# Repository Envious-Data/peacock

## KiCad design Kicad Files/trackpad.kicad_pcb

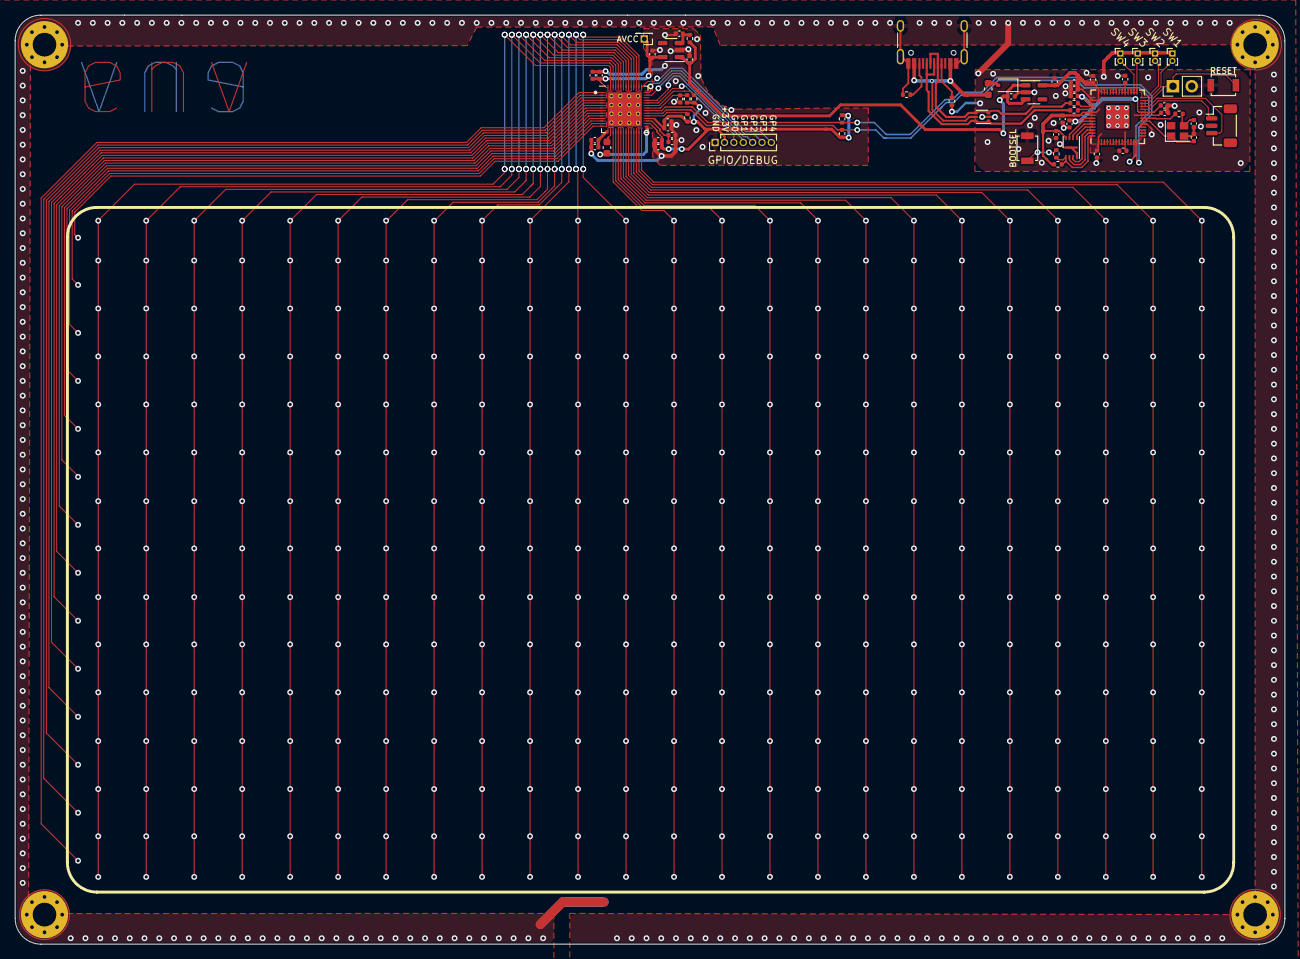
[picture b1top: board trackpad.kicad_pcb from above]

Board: 2 copper layers, 172.0 x 125.8 mm, 68 parts (0 on the bottom side), 46 nets.

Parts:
C1, C4, C14, C15, C18, C22, C28, C30: 1µ; C_0402_1005Metric
C2, C3, C5, C6, C7, C8, C9, C10, C11, C37: 100n; C_0402_1005Metric
C12, C13: 15p; C_0402_1005Metric
C16, C39: 10nF; C_0402_1005Metric
C17: 2.2nF; C_0603_1608Metric
C19, C21, C23, C25, C27: 22n; C_0402_1005Metric
C20, C24, C26: 2.2µ; C_0402_1005Metric
D1: B5817; D_SOD-323
F1: Polyfuse; Fuse_0603_1608Metric
H1, H2, H3, H4: MountingHole_Pad; MountingHole_3.2mm_M3_Pad_Via
J1: type-c-31-m-12; USB_C_Receptacle_HRO_TYPE-C-31-M-12
J3: JST 3P; JST_SH_BM03B-SRSS-TB_1x03-1MP_P1.00mm_Vertical
J5: Conn_01x07_Pin; PinHeader_1x07_P1.27mm_Vertical
J9: Conn_01x02_Pin; PinHeader_1x02_P2.54mm_Vertical
J10: Conn_01x01_Pin; PinHeader_1x01_P1.27mm_Vertical
R1, R11, R12, R17: 10k; R_0402_1005Metric
R2, R3: 1k; R_0402_1005Metric
R6, R7: 5.1k; R_0402_1005Metric
R8, R9: 27; R_0402_1005Metric
R10: 12k; R_0402_1005Metric
R13, R14: 3.3k; R_0402_1005Metric
SW1, SW2, SW3, SW4: SW_Push; PinHeader_1x02_P1.00mm_Vertical
SW_BOOT1: SW_Push; SW_SPST_B3U-1000P
SW_RST1: SW_Push; SW_SPST_B3U-1000P
U1: RP2040; QFN-56-1EP_7x7mm_P0.4mm_EP3.2x3.2mm
U2: W25Q16JVUXIQ; USON-8-1EP_3x2mm_P0.5mm_EP0.25x1.65mm
U3, U5: MIC5504-3.3YM5; SOT-23-5
U4: mXT336UD-MAU002; QFN-56_EP_6x6_Pitch0.35mm
U7: USBLC6-2P6; SOT-666
Y1: Crystal_GND24; Crystal_SMD_2520-4Pin_2.5x2.0mm

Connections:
3V3: C4.1, C5.1, C6.1, C7.1, C8.1, C9.1, C10.1, C11.1, C30.1, C37.2, R1.1, U1.1 (IOVDD), U1.10 (IOVDD), U1.22 (IOVDD), U1.33 (IOVDD), U1.42 (IOVDD), U1.43 (ADC_AVDD), U1.44 (VREG_IN), U1.48 (USB_VDD), U1.49 (IOVDD), U2.8 (VCC), U3.5 (VOUT)
5V: C14.1, C15.1, D1.1 (K), R17.1, U3.1 (VIN), U3.3 (EN), U5.1 (VIN)
+1V1: C1.1, C2.1, C3.1, U1.23 (DVDD), U1.45 (VREG_VOUT), U1.50 (DVDD)
+3.3VA: C20.2, C21.2, C28.1, J10.1, U4.56 (AVDD), U5.5 (VOUT)
+3V3: C24.2, C25.2, C26.2, C27.2, J5.2, R10.1, R11.1, R12.1, R13.1, R14.1, U4.30 (VDD), U4.32 (VDDIO)
/Macropad/D+: J1.A6 (D+), J1.B6 (D+), R8.2, U7.1 (I/O1), U7.6 (I/O1)
/Macropad/D-: J1.A7 (D-), J1.B7 (D-), R9.2, U7.3 (I/O2), U7.4 (I/O2)
/Macropad/RUN: J9.1, SW_RST1.1, U1.26 (RUN)
/Macropad/SW1: SW1.2, U1.27 (GPIO16)
/Macropad/SW2: SW2.2, U1.28 (GPIO17)
/Macropad/SW3: SW3.2, U1.29 (GPIO18)
/Macropad/SW4: SW4.2, U1.30 (GPIO19)
/Sensor/CHANGE: R11.2, U4.37 (CHG)
/Sensor/GPIO0: J5.3, U4.38 (GPIO0)
/Sensor/GPIO1: J5.4, U4.39 (GPIO1)
/Sensor/GPIO2: J5.5, U4.41 (GPIO2)
/Sensor/GPIO3: J5.6, U4.42 (GPIO3)
/Sensor/GPIO4: J5.7, U4.43 (GPIO4)
/Sensor/RESET: C16.1, R10.2, U4.36 (RESET)
GND: C1.2, C2.2, C3.2, C4.2, C5.2, C6.2, C7.2, C8.2, C9.2, C10.2, C11.2, C12.2, C13.2, C14.2, C15.2, C16.2, C18.2, C19.2, C20.1, C21.1, C22.1, C23.1, C24.1, C25.1, C26.1, C27.1, C28.2, C30.2, C37.1, C39.2, H1.1, H2.1, H3.1, H4.1, J1.A1 (GND), J1.A12 (GND), J1.B1 (GND), J1.B12 (GND), J1.S1 (SHIELD), J3.2, J5.1, J9.2, R6.2, R7.2, SW1.1, SW2.1, SW3.1, SW4.1, SW_BOOT1.1, SW_RST1.2, U1.19 (TESTEN), U1.57 (GND), U2.4 (GND), U2.9 (EP), U3.2 (GND), U4.57 (GND), U5.2 (GND), U7.2 (GND), Y1.2, Y1.4
unnamed: C13.1, R3.2, Y1.3
unnamed: D1.2 (A), F1.1
unnamed: J1.A5 (CC1), R6.1
unnamed: J1.B5 (CC2), R7.1
unnamed: J3.1, U1.24 (SWCLK)
unnamed: J3.3, U1.25 (SWD)
unnamed: R2.1, SW_BOOT1.2
unnamed: U1.52 (QSPI_SCLK), U2.6 (CLK)
unnamed: U1.53 (QSPI_SD0), U2.5 (DI(IO0))
unnamed: U1.55 (QSPI_SD1), U2.2 (DO(IO1))
unnamed: U1.54 (QSPI_SD2), U2.3 (IO2)
unnamed: U1.51 (QSPI_SD3), U2.7 (IO3)
unnamed: R1.2, R2.2, U1.56 (QSPI_SS), U2.1 (~CS)
unnamed: R9.1, U1.46 (USB_DM)
unnamed: R8.1, U1.47 (USB_DP)
unnamed: C12.1, U1.20 (XIN), Y1.1
unnamed: R3.1, U1.21 (XOUT)
unnamed: C17.2, U4.29 (EXCAP0)
unnamed: C17.1, U4.16 (EXCAP1)
unnamed: R12.2, U4.33 (TEST)
unnamed: C22.2, C23.2, U4.31 (VDDCORE)
unnamed: C18.1, C19.1, U4.15 (XVDD)
unnamed: C39.1, R17.2, U5.3 (EN)
SCL: R13.2, U1.14 (GPIO11), U4.35 (SCL)
SDA: R14.2, U1.13 (GPIO10), U4.34 (SDA)
VBUS: F1.2, J1.A4 (VBUS), J1.A9 (VBUS), J1.B4 (VBUS), J1.B9 (VBUS), U7.5 (VBUS)

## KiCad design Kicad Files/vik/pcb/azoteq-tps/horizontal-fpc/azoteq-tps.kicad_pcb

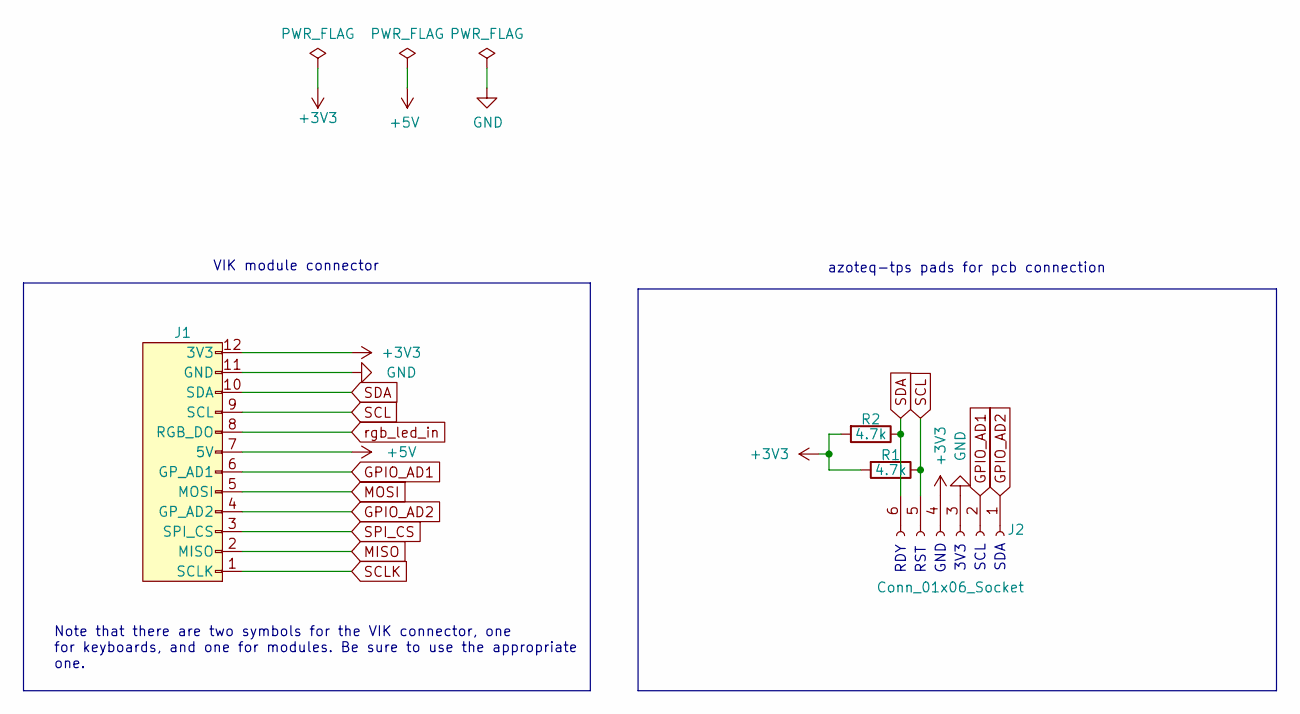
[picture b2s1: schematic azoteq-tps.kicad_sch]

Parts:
J1: vik-module-connector-horizontal-mini; LCSC C2919479
J2: Conn_01x06_Socket; Pad_06_2.00mm
R1, R2: 4.7k; R_0805_2012Metric_Pad1.20x1.40mm_HandSolder; LCSC C115310

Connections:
+3V3: J1.12 (3V3), J2.4, R1.2, R2.2
+5V: J1.7 (5V)
GND: J1.11 (GND), J2.3
GPIO_AD1: J1.6 (GPIO_AD1), J2.2
GPIO_AD2: J1.4 (GPIO_AD2), J2.1
MISO: J1.2 (MISO)
MOSI: J1.5 (MOSI)
SCL: J1.9 (SCL), J2.5, R1.1
SCLK: J1.1 (SCLK)
SDA: J1.10 (SDA), J2.6, R2.1
SPI_CS: J1.3 (SPI_CS)
rgb_led_in: J1.8 (RGB_LED_IN)

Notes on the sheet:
GND
RST
SCL
Note that there are two symbols for the VIK connector, one for keyboards, and one for modules. Be sure to use the appropriate one.
azoteq-tps pads for pcb connection
3V3
SDA
VIK module connector
RDY

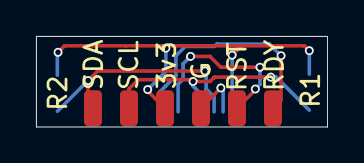
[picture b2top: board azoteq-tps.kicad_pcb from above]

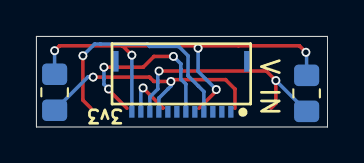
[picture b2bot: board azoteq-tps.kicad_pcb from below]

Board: 2 copper layers, 16.2 x 5.0 mm, 4 parts (3 on the bottom side), 6 nets.

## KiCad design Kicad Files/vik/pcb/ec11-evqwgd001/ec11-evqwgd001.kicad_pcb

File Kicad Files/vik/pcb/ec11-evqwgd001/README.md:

# ec11 evqwgd001 vik module

## Overview

This is a simple EC11 and EVQWGD001 vik module. It has support for 4 upwards facing SK6812 mini-e leds, in case you want to add a little pizzazz to your encoder.

Please note that this PCB does **not** support the click, only rotation of the encoder.

## Fabrication and BOM

For PCB fabrication, you can use the files in the production folder.

* gerbers.zip - the file used to fabricate the pcb
* bom.csv - used for PCBA. You can also use the part numbers in this file to look up the exact parts as [lcsc.com](https://lcsc.com)
* positions.csv - used for PCBA

Using the 3 files above, this has been tested at [jlcpcb.com](https://jlcpcb.com)

## VIK module certification

| Category                | Classification          | Response           |
| ----------------------- | ----------------------- | ------------------ |
| FPC connector           | Required                | :heavy_check_mark: |
| Breakout pins           | Recommended             | :x:                |
| Uses: SPI               | Optional                | :x:                |
| SPI used for SPI only   | Strongly recommended    | N/A                |
| Uses: I2C               | Optional                | :x:                |
| I2C used for I2C only   | Strongly Recommended    | :x:                |
| I2C pull ups            | Required                | N/A                |
| Uses: RGB               | Optional                | :heavy_check_mark: |
| Uses: Extra GPIO 1      | Optional                | :heavy_check_mark: |
| Uses: Extra GPIO 2      | Optional                | :heavy_check_mark: |
| Standard PCB Size/Mount | Strongly recommended    | :x:                |

## PCB images

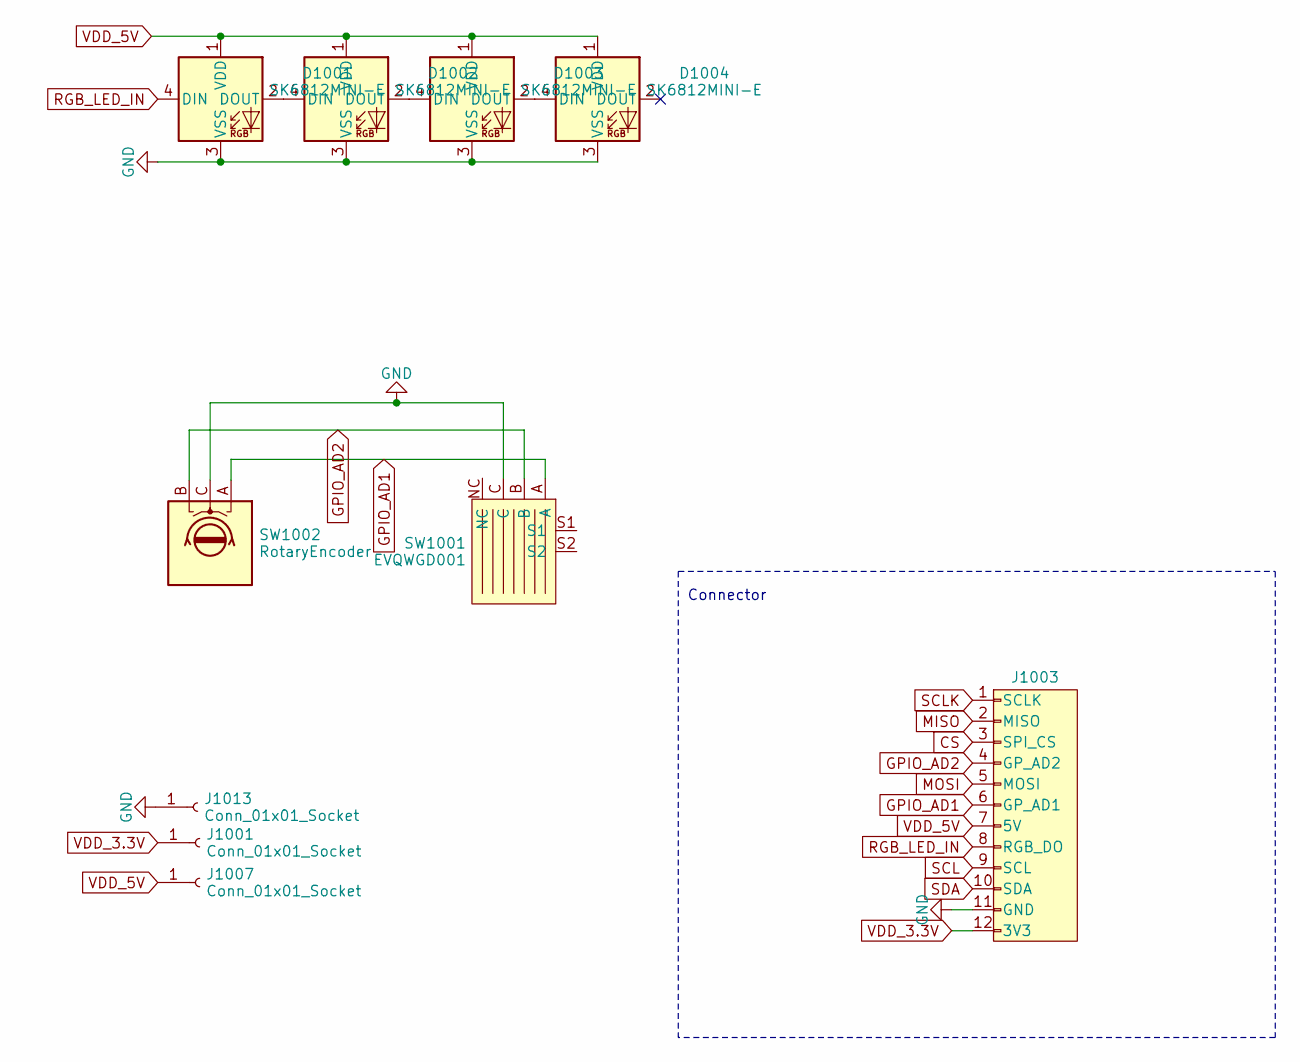
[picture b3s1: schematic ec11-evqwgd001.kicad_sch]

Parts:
D1001, D1002, D1003, D1004: SK6812MINI-E; SK6812MINI-E-no-switch-outline
J1001, J1007, J1013: Conn_01x01_Socket; SolderWire-0.5sqmm_1x01_D0.9mm_OD2.3mm
J1003: vik-module-connector-horizontal; LCSC C2919557
SW1001: EVQWGD001
SW1002: RotaryEncoder; RotaryEncoder_EC11-no-legs

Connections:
CS: J1003.3 (SPI_CS)
GND: D1001.3 (VSS), D1002.3 (VSS), D1003.3 (VSS), D1004.3 (VSS), J1003.11 (GND), J1013.1, SW1001.C, SW1002.C
GPIO_AD1: J1003.6 (GPIO_AD1), SW1001.A, SW1002.A
GPIO_AD2: J1003.4 (GPIO_AD2), SW1001.B, SW1002.B
MISO: J1003.2 (MISO)
MOSI: J1003.5 (MOSI)
unnamed: D1001.2 (DOUT), D1002.4 (DIN)
unnamed: D1002.2 (DOUT), D1003.4 (DIN)
unnamed: D1003.2 (DOUT), D1004.4 (DIN)
RGB_LED_IN: D1001.4 (DIN), J1003.8 (RGB_LED_IN)
SCL: J1003.9 (SCL)
SCLK: J1003.1 (SCLK)
SDA: J1003.10 (SDA)
VDD_3.3V: J1001.1, J1003.12 (3V3)
VDD_5V: D1001.1 (VDD), D1002.1 (VDD), D1003.1 (VDD), D1004.1 (VDD), J1003.7 (5V), J1007.1

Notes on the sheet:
Connector

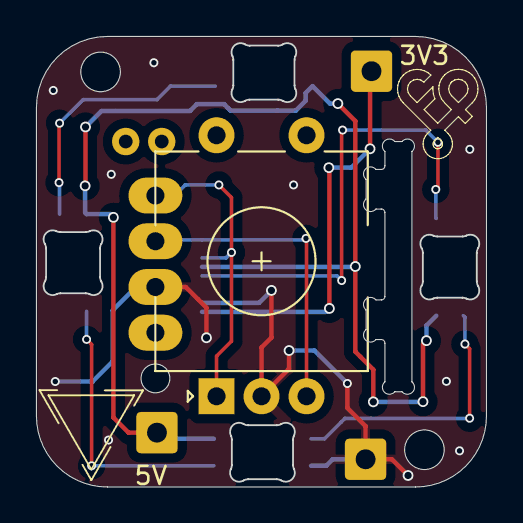
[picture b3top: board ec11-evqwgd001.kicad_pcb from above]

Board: 2 copper layers, 25.0 x 25.0 mm, 10 parts (1 on the bottom side), 9 nets.

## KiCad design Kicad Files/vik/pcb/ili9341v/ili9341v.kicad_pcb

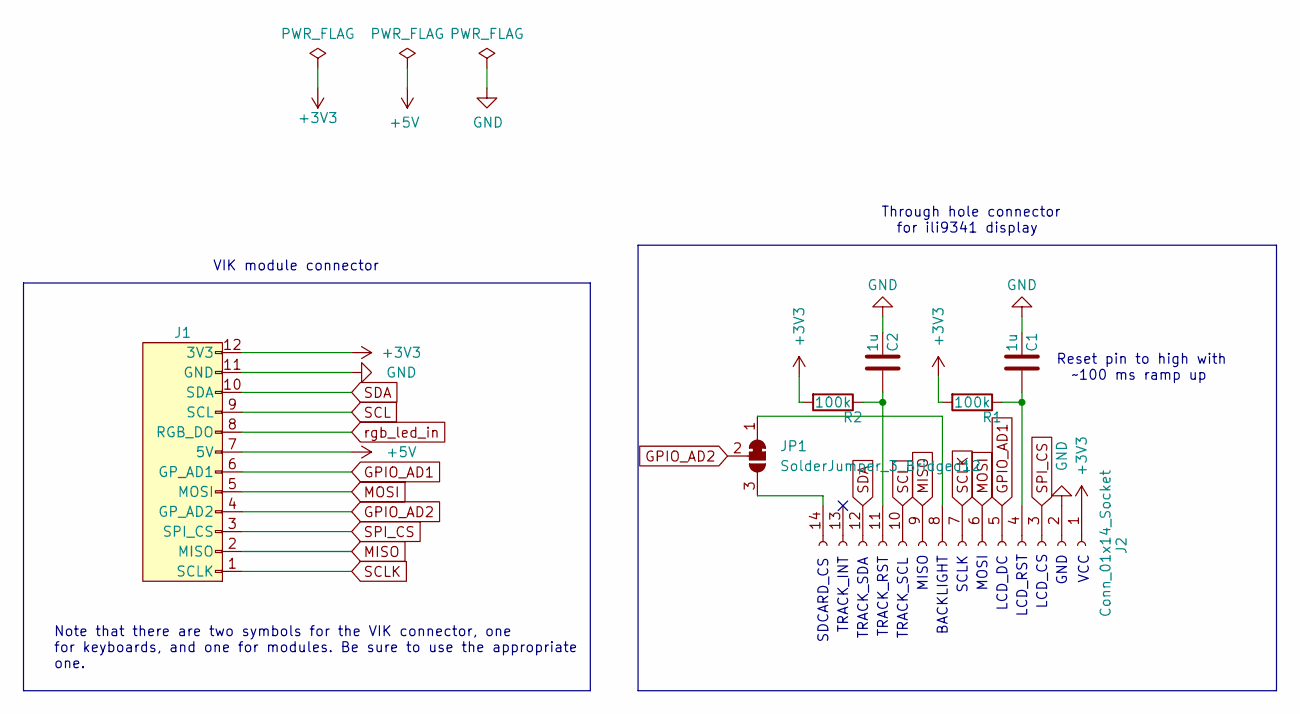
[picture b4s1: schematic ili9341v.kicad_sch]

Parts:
C1, C2: 1u; C_0402_1005Metric; MPN CL05A105KA5NQNC; LCSC C52923
J1: vik-module-connector-horizontal; LCSC C479750
J2: Conn_01x14_Socket; PinHeader_1x14_P2.54mm_Vertical
JP1: SolderJumper_3_Bridged12; SolderJumper-3_P1.3mm_Bridged12_RoundedPad1.0x1.5mm_NumberL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
R1, R2: 100k; R_1206_3216Metric_Pad1.30x1.75mm_HandSolder; LCSC C17900

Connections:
+3V3: J1.12 (3V3), J2.1, R1.2, R2.2
+5V: J1.7 (5V)
GND: C1.1, C2.1, J1.11 (GND), J2.2
GPIO_AD1: J1.6 (GP_AD1), J2.5
GPIO_AD2: J1.4 (GP_AD2), JP1.2 (C)
MISO: J1.2 (MISO), J2.9
MOSI: J1.5 (MOSI), J2.6
unnamed: C1.2, J2.4, R1.1
unnamed: J2.8, JP1.1 (A)
unnamed: C2.2, J2.11, R2.1
unnamed: J2.14, JP1.3 (B)
SCL: J1.9 (SCL), J2.10
SCLK: J1.1 (SCLK), J2.7
SDA: J1.10 (SDA), J2.12
SPI_CS: J1.3 (SPI_CS), J2.3
rgb_led_in: J1.8 (RGB_DO)

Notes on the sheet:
LCD_DC
VCC
TRACK_INT
TRACK_SDA
LCD_CS
SCLK
Note that there are two symbols for the VIK connector, one for keyboards, and one for modules. Be sure to use the appropriate one.
Through hole connector for ili9341 display
MOSI
SDCARD_CS
BACKLIGHT
VIK module connector
Reset pin to high with ~100 ms ramp up
LCD_RST
GND
TRACK_RST
MISO
TRACK_SCL

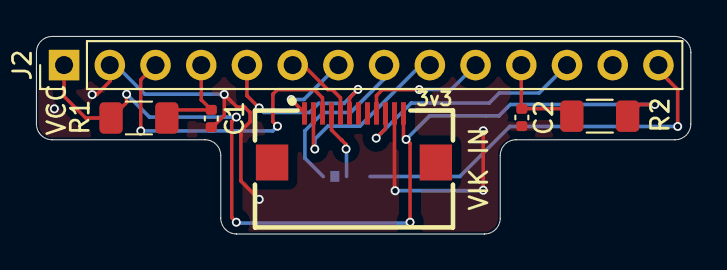
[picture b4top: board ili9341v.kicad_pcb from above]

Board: 2 copper layers, 36.4 x 11.0 mm, 7 parts (1 on the bottom side), 14 nets.

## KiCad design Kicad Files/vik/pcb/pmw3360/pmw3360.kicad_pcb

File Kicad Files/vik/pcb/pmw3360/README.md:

# PMW3360 trackball pcb

## Overview

This is a VIK module to use a PMW3360 motion sensor. This sensor is primarily used for mousing applications, and is supported in [QMK](https://github.com/qmk_firmware/qmk)

The most common use in the keyboard community is for trackballs.

Note that while I2C, RGB, and extra GPIO are broken out, but are not used in the circuitry, so they are not needed for the sensor. There are also footprints for I2C pull up resistors, which are also not needed, as I2C is not used.

## Fabrication and BOM

For PCB fabrication, you can use the files in the production folder.

* gerbers.zip - the file used to fabricate the pcb
* bom.csv - used for PCBA. You can also use the part numbers in this file to look up the exact parts as [lcsc.com](https://lcsc.com)
* positions.csv - used for PCBA

Using the 3 files above, this has been tested at [jlcpcb.com](https://jlcpcb.com)

## VIK module certification

| Category                | Classification          | Response           |
| ----------------------- | ----------------------- | ------------------ |
| FPC connector           | Required                | :heavy_check_mark: |
| Breakout pins           | Recommended             | :heavy_check_mark: |
| Uses: SPI               | Optional                | :heavy_check_mark: |
| SPI used for SPI only   | Strongly recommended    | :heavy_check_mark: |
| Uses: I2C               | Optional                | :x:                |
| I2C used for I2C only   | Strongly Recommended    | :x:                |
| I2C pull ups            | Required                | N/A                |
| Uses: RGB               | Optional                | :x:                |
| Uses: Extra GPIO 1      | Optional                | :x:                |
| Uses: Extra GPIO 2      | Optional                | :x:                |
| Standard PCB Size/Mount | Strongly recommended    | Small              |

## PCB images

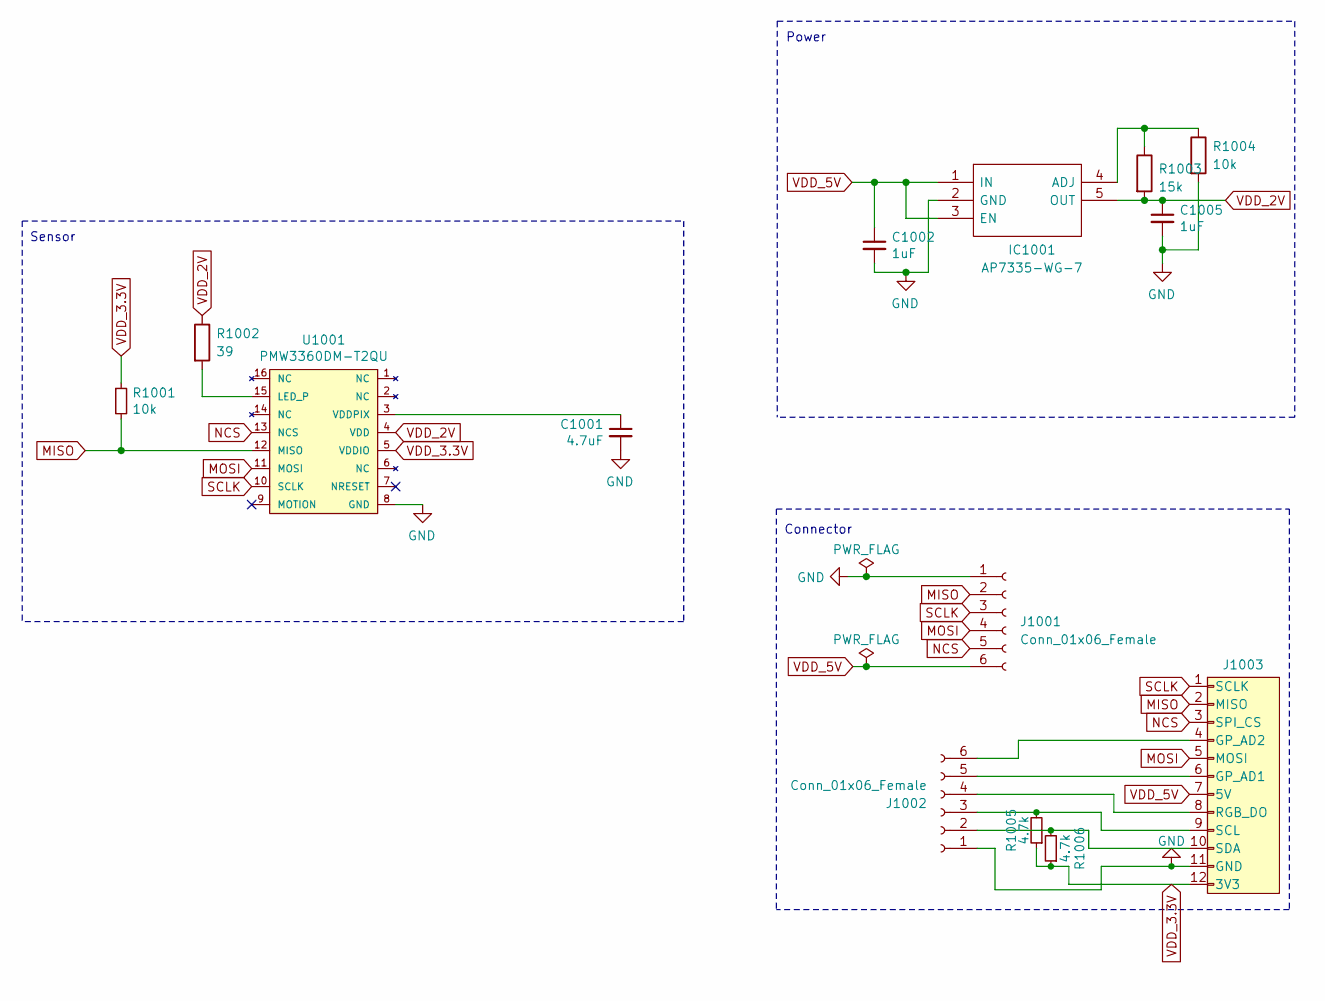
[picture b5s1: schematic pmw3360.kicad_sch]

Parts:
C1001: 4.7uF; C_0603_1608Metric; LCSC C19666
C1002, C1005: 1uF; C_0603_1608Metric; LCSC C15849
IC1001: AP7335-WG-7; SOT-23-5_HandSoldering; Manufacturer_Part_Number AP7331-WG-7; Mouser Part Number 621-AP7331-WG-7
J1001, J1002: Conn_01x06_Female; PinHeader_1x06_P2.54mm_Vertical
J1003: vik-module-connector-horizontal; LCSC C479750
R1001, R1004: 10k; R_0603_1608Metric; LCSC C25804
R1002: 39; R_0603_1608Metric; LCSC C23154
R1003: 15k; R_0603_1608Metric; LCSC C22809
R1005, R1006: 4.7k; D3_TH_SMD
U1001: PMW3360DM-T2QU; DIP-16_W10.16mm

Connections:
GND: C1001.2, C1002.2, C1005.2, IC1001.2 (GND), J1001.1, J1002.1, J1003.11 (GND), R1004.2, U1001.8 (GND)
MISO: J1001.2, J1003.2 (MISO), R1001.2, U1001.12 (MISO)
MOSI: J1001.4, J1003.5 (MOSI), U1001.11 (MOSI)
NCS: J1001.5, J1003.3 (SPI_CS), U1001.13 (NCS)
unnamed: IC1001.4 (ADJ), R1003.1, R1004.1
unnamed: J1002.2, J1003.10 (SDA), R1006.2
unnamed: J1002.3, J1003.9 (SCL), R1005.2
unnamed: J1002.4, J1003.8 (RGB_LED_IN)
unnamed: J1002.5, J1003.6 (GPIO_AD1)
unnamed: J1002.6, J1003.4 (GPIO_AD2)
unnamed: R1002.2, U1001.15 (LED_P)
unnamed: C1001.1, U1001.3 (VDDPIX)
SCLK: J1001.3, J1003.1 (SCLK), U1001.10 (SCLK)
VDD_2V: C1005.1, IC1001.5 (OUT), R1002.1, R1003.2, U1001.4 (VDD)
VDD_3.3V: J1003.12 (3V3), R1001.1, R1005.1, R1006.1, U1001.5 (VDDIO)
VDD_5V: C1002.1, IC1001.1 (IN), IC1001.3 (EN), J1001.6, J1003.7 (5V)

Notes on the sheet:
Power
Sensor
Connector

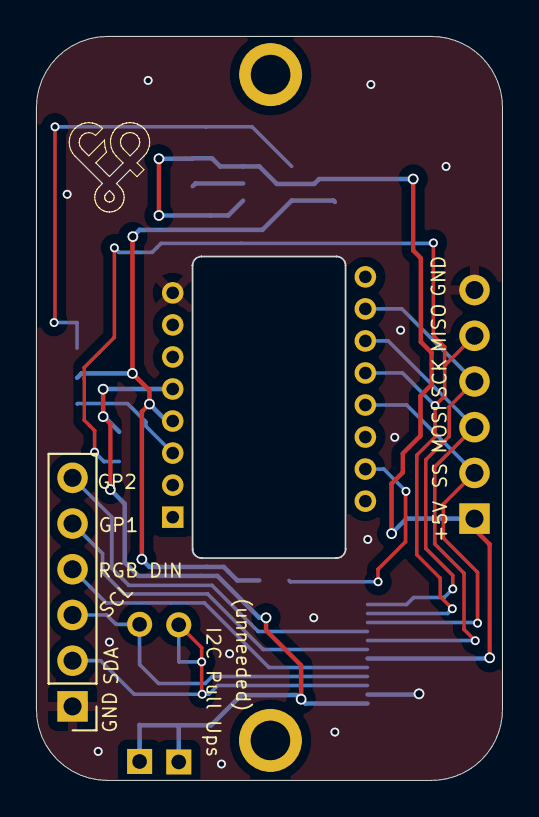
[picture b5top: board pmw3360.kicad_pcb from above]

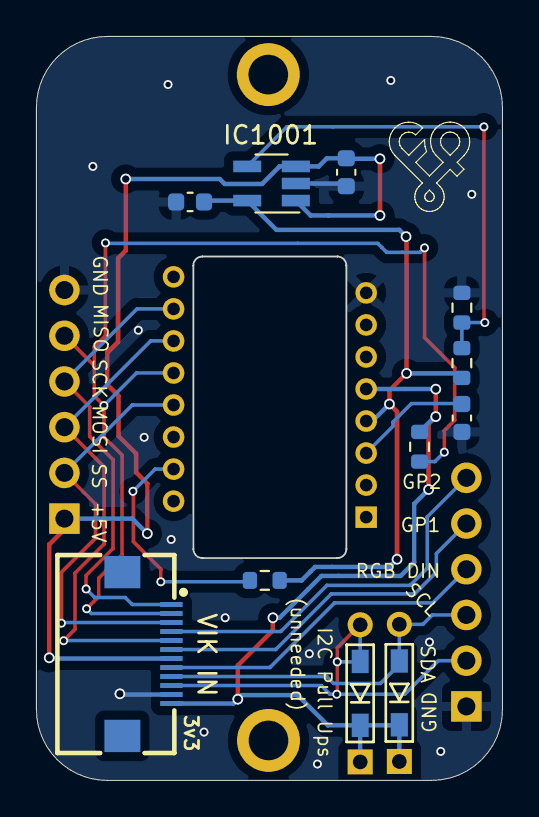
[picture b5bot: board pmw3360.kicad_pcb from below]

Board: 2 copper layers, 25.9 x 41.3 mm, 14 parts (12 on the bottom side), 16 nets.

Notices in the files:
Kicad Files/vik/pcb/ec11-evqwgd001/ec11-evqwgd001.kicad_sch:
Copyright Quentin Lebastard
